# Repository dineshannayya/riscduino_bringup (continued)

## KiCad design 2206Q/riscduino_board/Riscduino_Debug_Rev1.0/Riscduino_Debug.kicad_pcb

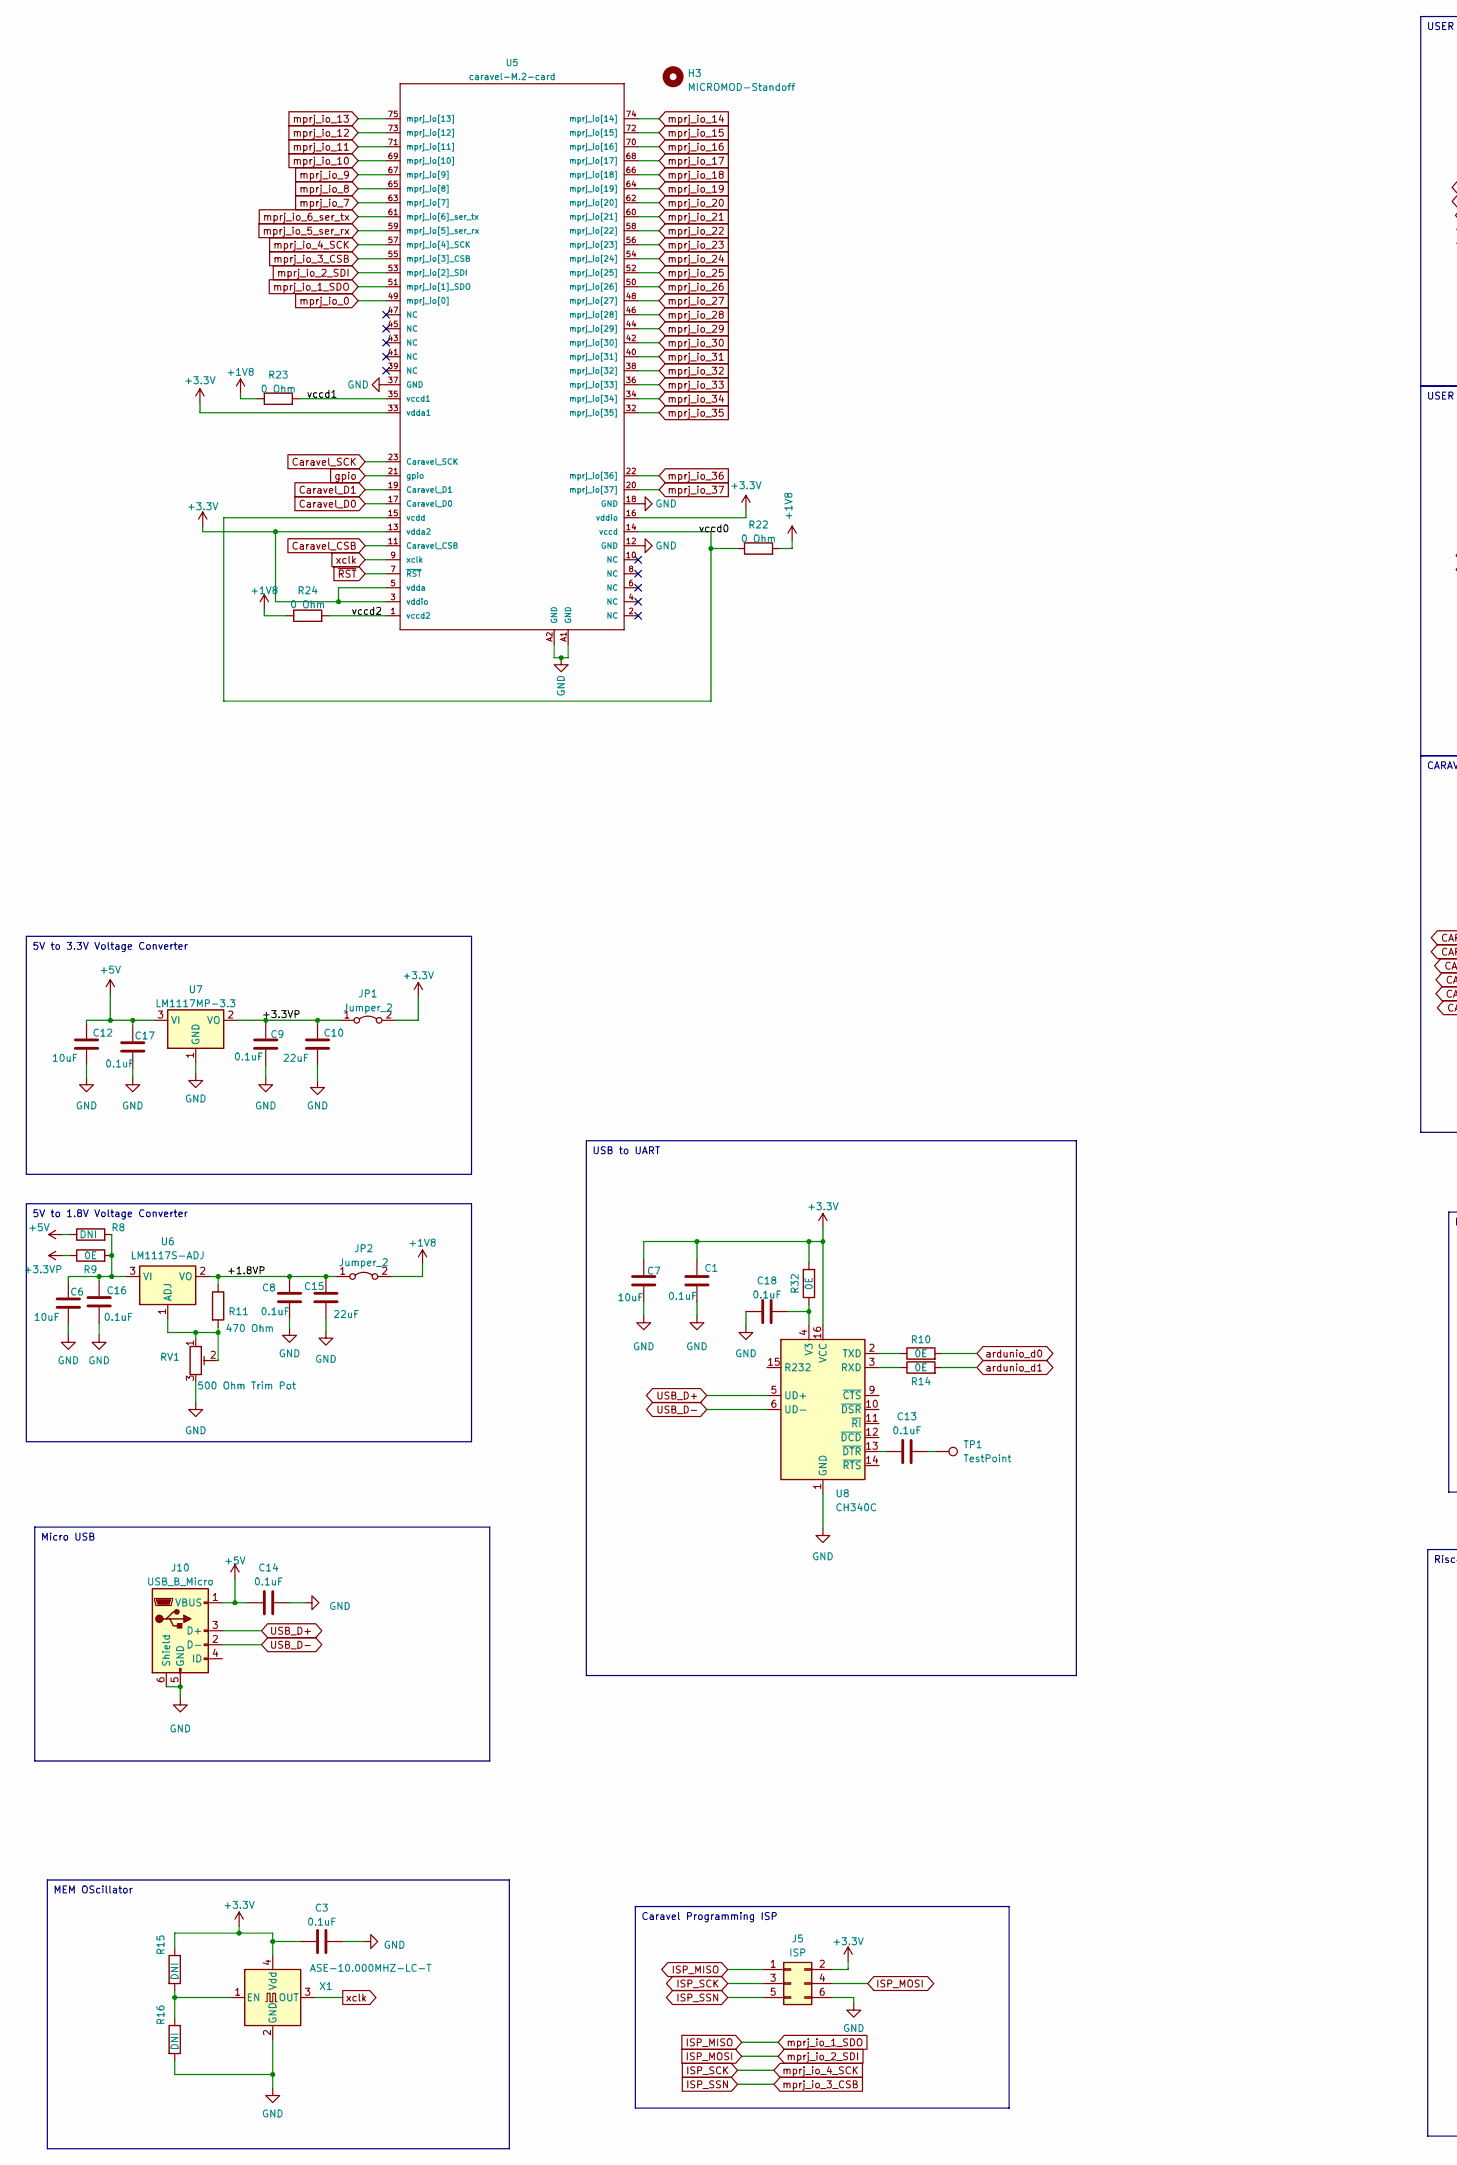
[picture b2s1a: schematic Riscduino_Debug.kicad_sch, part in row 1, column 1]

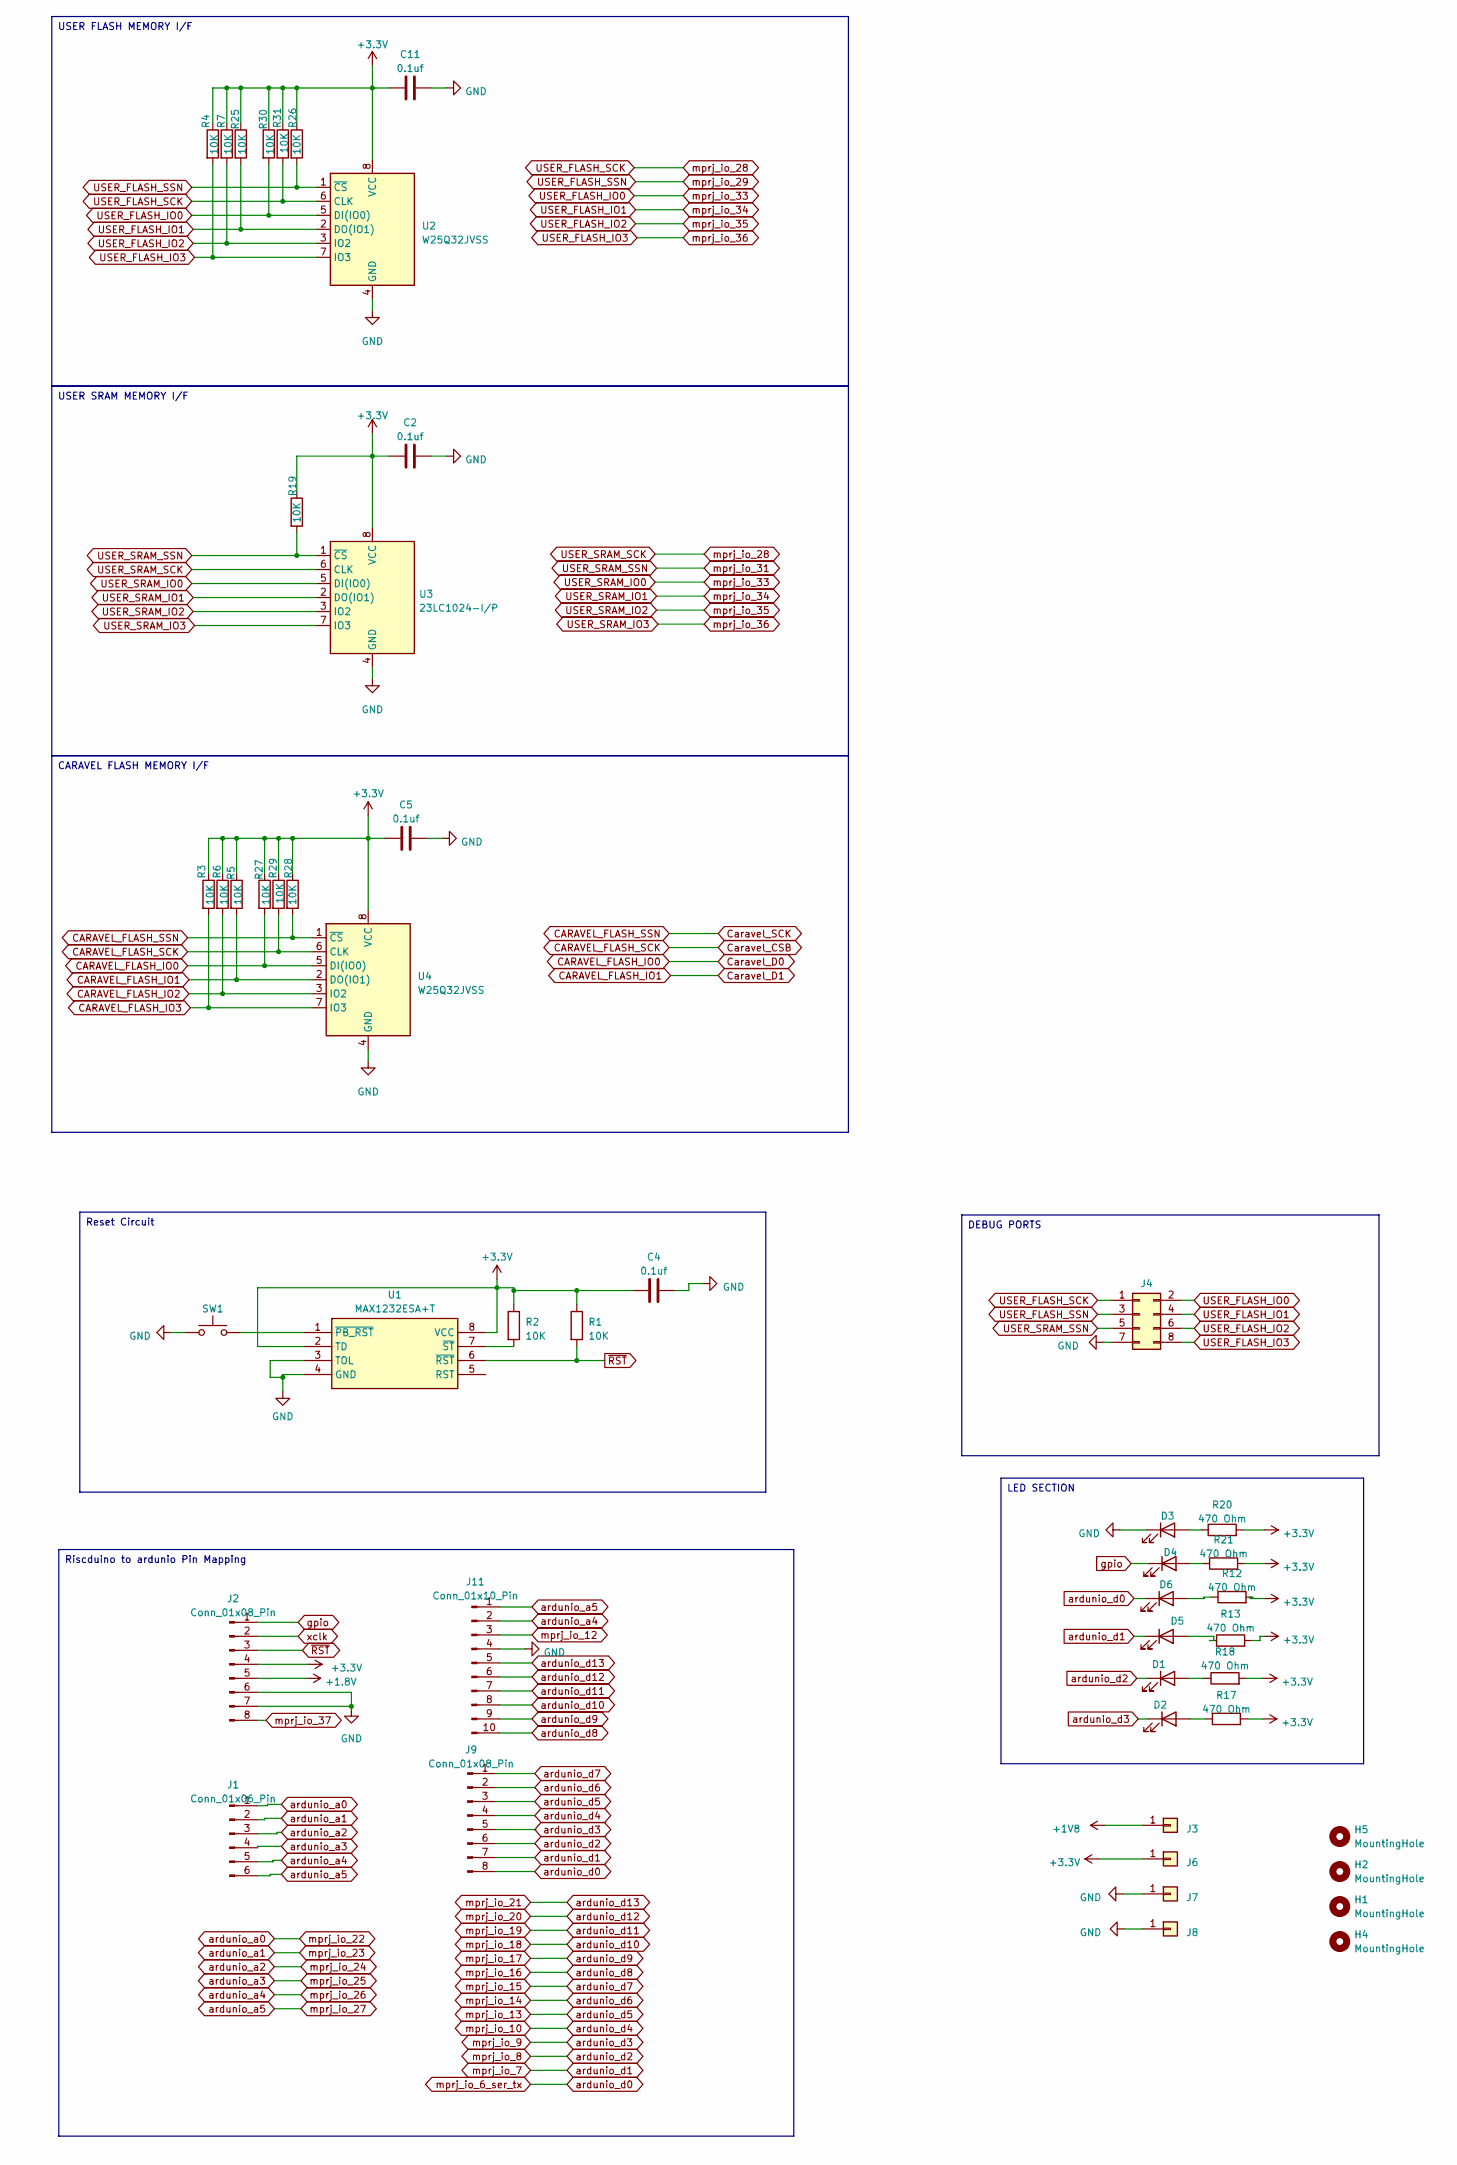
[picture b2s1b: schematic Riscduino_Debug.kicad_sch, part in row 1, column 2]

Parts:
C1, C3, C8, C9, C13, C14, C16, C17, C18: 0.1uF; C_0603_1608Metric_Pad1.08x0.95mm_HandSolder
C2, C4, C5, C11: 0.1uf; C_0603_1608Metric_Pad1.08x0.95mm_HandSolder
C6: 10uF; SW_SPST_CK_KXT3
C7, C12: 10uF; C_0805_2012Metric_Pad1.18x1.45mm_HandSolder
C10, C15: 22uF; C_0805_2012Metric_Pad1.18x1.45mm_HandSolder
D1, D2, D4, D5: GREEN LED; LED_0805_2012Metric_Pad1.15x1.40mm_HandSolder
D3: RED LED; LED_0805_2012Metric_Pad1.15x1.40mm_HandSolder
D6: BLUE LED; LED_0805_2012Metric_Pad1.15x1.40mm_HandSolder
H1, H2, H4, H5: MountingHole; MountingHole_3.2mm_M3
H3: MICROMOD-Standoff; MicroMod-Standoff
J1: Conn_01x06_Pin; PinHeader_1x06_P2.54mm_Vertical
J2, J9: Conn_01x08_Pin; PinHeader_1x08_P2.54mm_Vertical
J3, J6, J7, J8: Conn_01x01; PinHeader_1x01_P2.54mm_Vertical
J4: Conn_02x04_Odd_Even; PinHeader_2x04_P2.54mm_Vertical
J5: ISP; PinHeader_2x03_P2.54mm_Vertical
J10: USB_B_Micro; USB_Micro-B_Molex-105017-0001
J11: Conn_01x10_Pin; PinHeader_1x10_P2.54mm_Vertical
JP1, JP2: Jumper_2; PinHeader_1x02_P2.54mm_Vertical
R1, R2, R3, R4, R5, R6, R7, R19, R25, R26, R27, R28, R29, R30, R31: 10K; R_0603_1608Metric_Pad0.98x0.95mm_HandSolder
R8, R15, R16: DNI; R_0603_1608Metric_Pad0.98x0.95mm_HandSolder
R9, R10, R14, R32: 0E; R_0603_1608Metric_Pad0.98x0.95mm_HandSolder
R11, R12, R13, R17, R18, R20, R21: 470 Ohm; R_0603_1608Metric_Pad0.98x0.95mm_HandSolder
R22, R23, R24: 0 Ohm; R_0603_1608Metric_Pad0.98x0.95mm_HandSolder
RV1: 500 Ohm Trim Pot; Potentiometer_Bourns_3296W_Vertical
SW1: 4Pin Round Button SPST Straight Tactile Switch SM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; SW_SPST_EVPBF_TS4550TP
TP1: TestPoint; PinHeader_1x01_P2.54mm_Vertical
U1: MAX1232ESA+T; SOIC-8-1EP_3.9x4.9mm_P1.27mm_EP2.29x3mm; Manufacturer_Part_Number MAX1232ESA+T; Mouser Part Number 700-MAX1232ESAT
U2, U4: W25Q32JVSS; SOIC-8_5.23x5.23mm_P1.27mm
U3: 23LC1024-I/P; DIP-8_W7.62mm_LongPads
U5: caravel-M.2-card; M.2-CONNECTOR-E
U6: LM1117S-ADJ; SOT-223-3_TabPin2
U7: LM1117MP-3.3; SOT-223-3_TabPin2
U8: CH340C; SOIC-16_3.9x9.9mm_P1.27mm
X1: ASE-10.000MHZ-LC-T; Crystal_SMD_Abracon_ABM8G-4Pin_3.2x2.5mm

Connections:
+3.3V: C1.1, C2.1, C3.1, C4.1, C5.1, C7.1, C11.1, J2.4, J5.2, J6.1, JP1.2 (B), R1.1, R2.1, R3.1, R4.1, R5.1, R6.1, R7.1, R12.2, R13.2, R15.1, R17.2, R18.2, R19.1, R20.2, R21.2, R25.1, R26.1, R27.1, R28.1, R29.1, R30.1, R31.1, R32.2, U1.2 (TD), U1.8 (VCC), U2.8 (VCC), U3.8 (VCC), U4.8 (VCC), U5.3 (vddio), U5.5 (vdda), U5.13 (vdda2), U5.16 (vddio), U5.33 (vdda1), U8.16 (VCC), X1.4 (Vdd)
+3.3VP: C9.1, C10.1, JP1.1 (A), R9.1, U7.2 (VO)
+5V: C12.1, C14.1, C17.1, J10.1 (VBUS), R8.1, U7.3 (VI)
/+1.8VP: C8.1, C15.1, JP2.1 (A), R11.1, U6.2 (VO)
CARAVEL_FLASH_IO0: R27.2, U4.5 (DI(IO0)), U5.17 (Caravel_D0)
CARAVEL_FLASH_IO1: R5.2, U4.2 (DO(IO1)), U5.19 (Caravel_D1)
CARAVEL_FLASH_IO2: R6.2, U4.3 (IO2)
CARAVEL_FLASH_IO3: R3.2, U4.7 (IO3)
CARAVEL_FLASH_SCK: R29.2, U4.6 (CLK), U5.11 (Caravel_CSB)
CARAVEL_FLASH_SSN: R28.2, U4.1 (~CS), U5.23 (Caravel_SCK)
GND: C1.2, C2.2, C3.2, C4.2, C5.2, C6.2, C7.2, C8.2, C9.2, C10.2, C11.2, C12.2, C14.2, C15.2, C16.2, C17.2, C18.1, D3.1 (K), J2.6, J2.7, J4.7, J5.6, J7.1, J8.1, J10.5 (GND), J10.6 (Shield), J11.4, R16.2, RV1.3, SW1.1, U1.3 (TOL), U1.4 (GND), U2.4 (GND), U3.4 (GND), U4.4 (GND), U5.12 (GND), U5.18 (GND), U5.37 (GND), U5.A1 (GND), U5.A2 (GND), U7.1 (GND), U8.1 (GND), X1.2 (GND)
ISP_MISO: J5.1, U5.51 (mprj_io[1]_SDO)
ISP_MOSI: J5.4, U5.53 (mprj_io[2]_SDI)
ISP_SCK: J5.3, U5.57 (mprj_io[4]_SCK)
ISP_SSN: J5.5, U5.55 (mprj_io[3]_CSB)
unnamed: C13.2, TP1.1
unnamed: D1.2 (A), R18.1
unnamed 17: D2.2 (A), R17.1; also elsewhere on the board
unnamed: D3.2 (A), R20.1
unnamed: D4.2 (A), R21.1
unnamed: D5.2 (A), R13.1
unnamed: D6.2 (A), R12.1
unnamed: SW1.2, U1.1 (~PB_RST)
unnamed: R2.2, U1.7 (~ST)
unnamed: R23.2, U5.35 (vccd1)
unnamed: R24.2, U5.1 (vccd2)
unnamed: R22.1, U5.14 (vccd), U5.15 (vcdd)
unnamed: R11.2, RV1.1, RV1.2, U6.1 (ADJ)
unnamed: C6.1, C16.1, R8.2, R9.2, U6.3 (VI)
unnamed: R14.1, U8.3 (RXD)
unnamed: R10.1, U8.2 (TXD)
unnamed: C18.2, R32.1, U8.4 (V3)
unnamed: C13.1, U8.13 (~DTR)
unnamed: R15.2, R16.1, X1.1 (EN)
USB_D+: J10.3 (D+), U8.5 (UD+)
USB_D-: J10.2 (D-), U8.6 (UD-)
USER_FLASH_IO0: J4.2, R30.2, U2.5 (DI(IO0)), U3.5 (DI(IO0)), U5.36 (mprj_io[33])
USER_FLASH_IO1: J4.4, R25.2, U2.2 (DO(IO1)), U3.2 (DO(IO1)), U5.34 (mprj_io[34])
USER_FLASH_IO2: J4.6, R7.2, U2.3 (IO2), U3.3 (IO2), U5.32 (mprj_io[35])
USER_FLASH_IO3: J4.8, R4.2, U2.7 (IO3), U3.7 (IO3), U5.22 (mprj_io[36])
USER_FLASH_SCK: J4.1, R31.2, U2.6 (CLK), U3.6 (CLK), U5.46 (mprj_io[28])
USER_FLASH_SSN: J4.3, R26.2, U2.1 (~CS), U5.44 (mprj_io[29])
USER_SRAM_SSN: J4.5, R19.2, U3.1 (~CS), U5.40 (mprj_io[31])
ardunio_a0: J1.1, U5.58 (mprj_io[22])
ardunio_a1: J1.2, U5.56 (mprj_io[23])
ardunio_a2: J1.3, U5.54 (mprj_io[24])
ardunio_a3: J1.4, U5.52 (mprj_io[25])
ardunio_a4: J1.5, J11.2, U5.50 (mprj_io[26])
ardunio_a5: J1.6, J11.1, U5.48 (mprj_io[27])
ardunio_d0: D6.1 (K), J9.8, R10.2, U5.61 (mprj_io[6]_ser_tx)
ardunio_d1: D5.1 (K), J9.7, R14.2, U5.63 (mprj_io[7])
ardunio_d2: D1.1 (K), J9.6, U5.65 (mprj_io[8])
ardunio_d3: D2.1 (K), J9.5, U5.67 (mprj_io[9]), U8.67; also elsewhere on the board
ardunio_d4: J9.4, U5.69 (mprj_io[10])
ardunio_d5: J9.3, U5.75 (mprj_io[13])
ardunio_d6: J9.2, U5.74 (mprj_io[14])
ardunio_d7: J9.1, U5.72 (mprj_io[15])
ardunio_d8: J11.10, U5.70 (mprj_io[16])
ardunio_d9: J11.9, U5.68 (mprj_io[17])
ardunio_d10: J11.8, U5.66 (mprj_io[18])
ardunio_d11: J11.7, U5.64 (mprj_io[19])
ardunio_d12: J11.6, U5.62 (mprj_io[20])
ardunio_d13: J11.5, U5.60 (mprj_io[21])
gpio: D4.1 (K), J2.1, U5.21 (gpio)
mprj_io_0: U5.49 (mprj_io[0])
mprj_io_5_ser_rx: U5.59 (mprj_io[5]_ser_rx)
mprj_io_11: U5.71 (mprj_io[11])
mprj_io_12: J11.3, U5.73 (mprj_io[12])
mprj_io_30: U5.42 (mprj_io[30])
mprj_io_32: U5.38 (mprj_io[32])
mprj_io_37: J2.8, U5.20 (mprj_io[37])
xclk: J2.2, U5.9 (xclk), X1.3 (OUT)
~RST: J2.3, R1.2, U1.6 (~RST), U5.7 (~RST)

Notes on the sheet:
MEM OScillator
5V to 3.3V Voltage Converter
LED SECTION
Riscduino to ardunio Pin Mapping
Micro USB
USB to UART
USER SRAM MEMORY I/F
DEBUG PORTS
Caravel Programming ISP
USER FLASH MEMORY I/F
5V to 1.8V Voltage Converter
Reset Circuit
CARAVEL FLASH MEMORY I/F

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
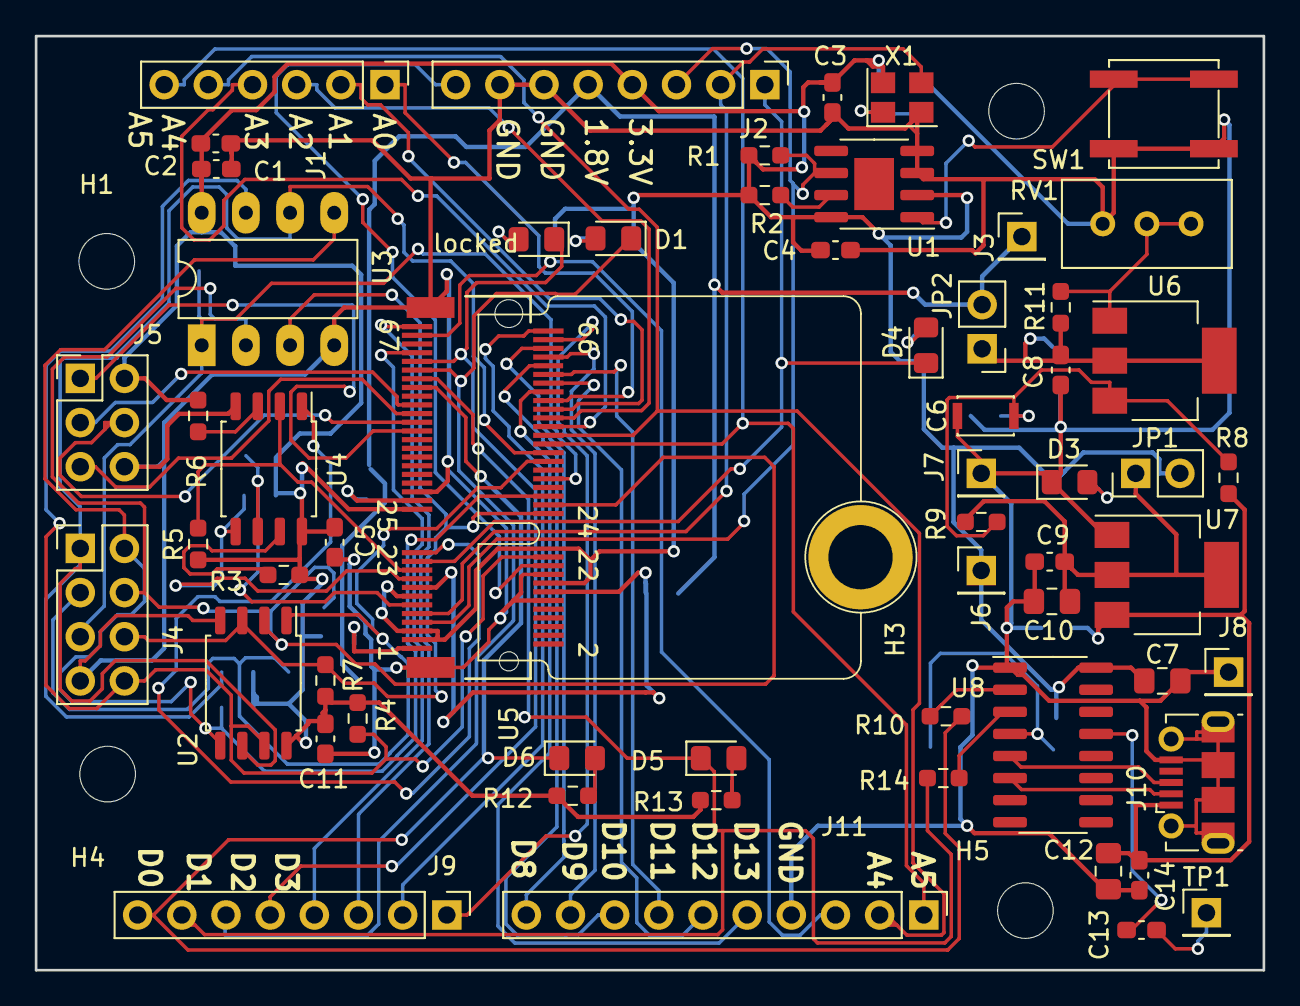
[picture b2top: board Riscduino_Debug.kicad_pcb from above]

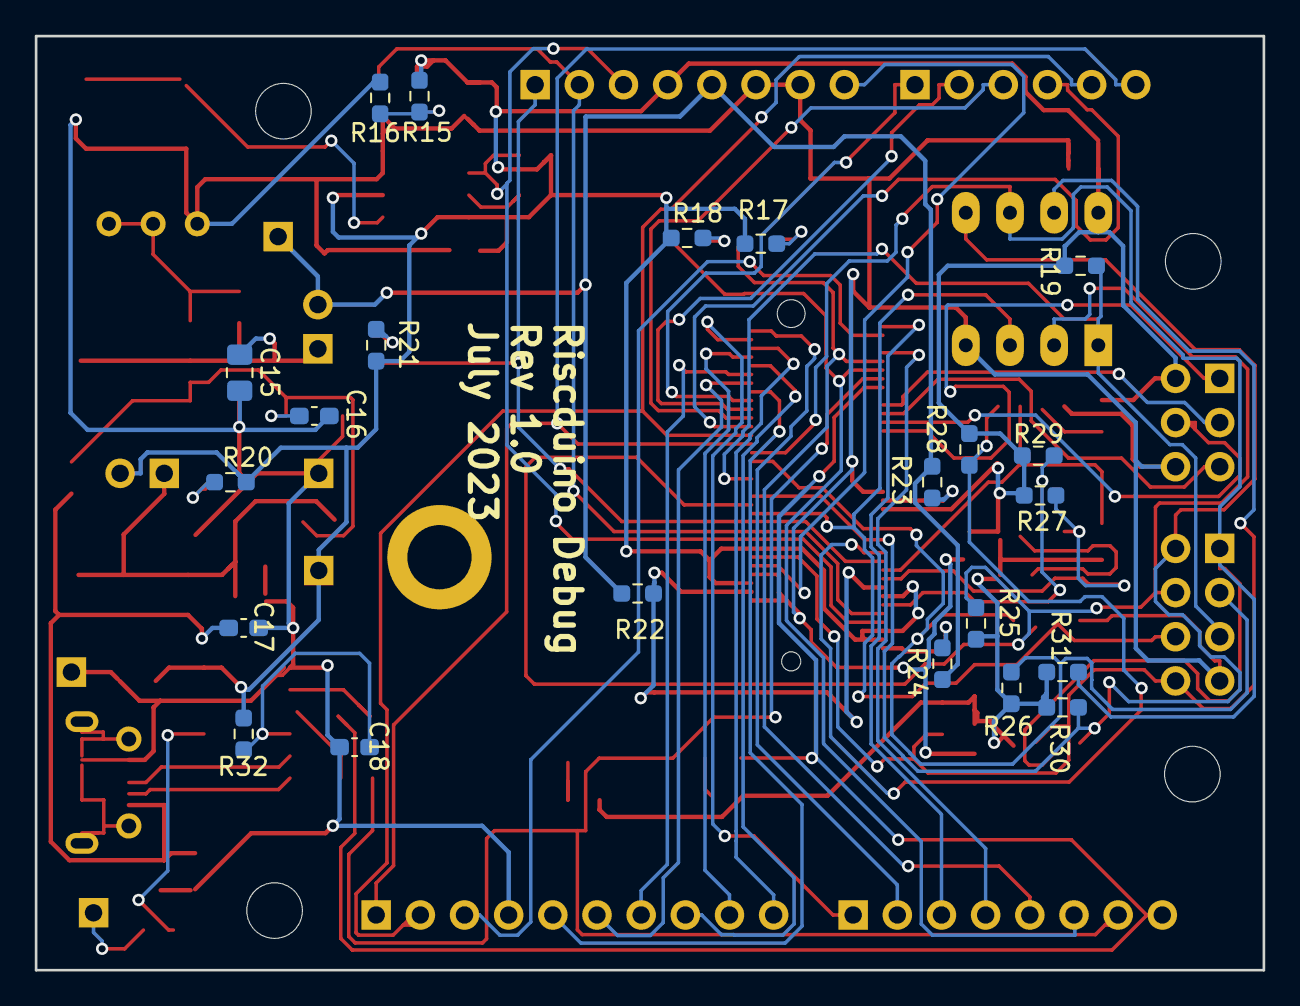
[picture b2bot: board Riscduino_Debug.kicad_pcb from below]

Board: 2 copper layers, 70.6 x 53.7 mm, 86 parts (22 on the bottom side), 69 nets.

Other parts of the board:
locked: GREEN LED; LED_0805_2012Metric_Pad1.15x1.40mm_HandSolder

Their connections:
unnamed 17: locked.2 (A); also elsewhere on the board
ardunio_d3: locked.1 (K); also elsewhere on the board

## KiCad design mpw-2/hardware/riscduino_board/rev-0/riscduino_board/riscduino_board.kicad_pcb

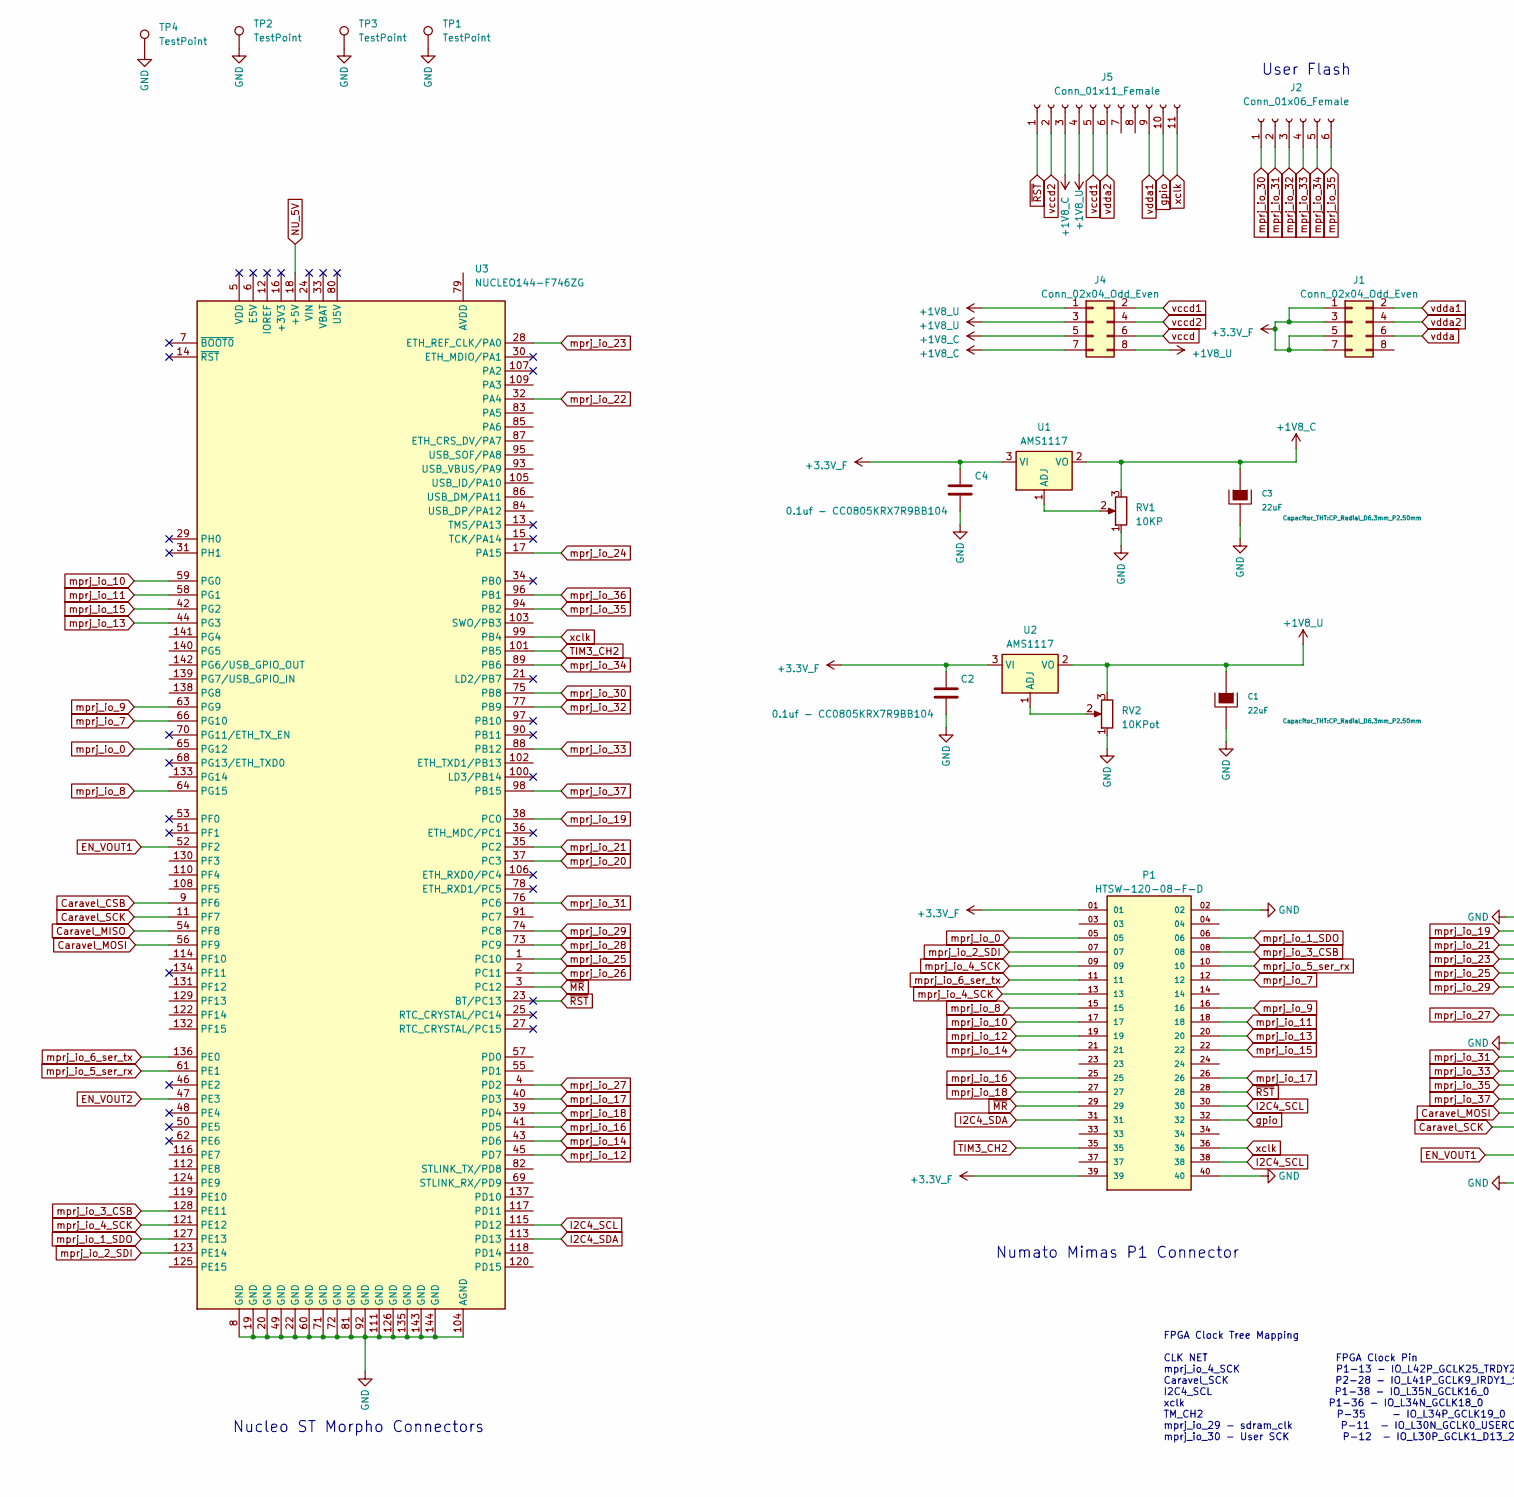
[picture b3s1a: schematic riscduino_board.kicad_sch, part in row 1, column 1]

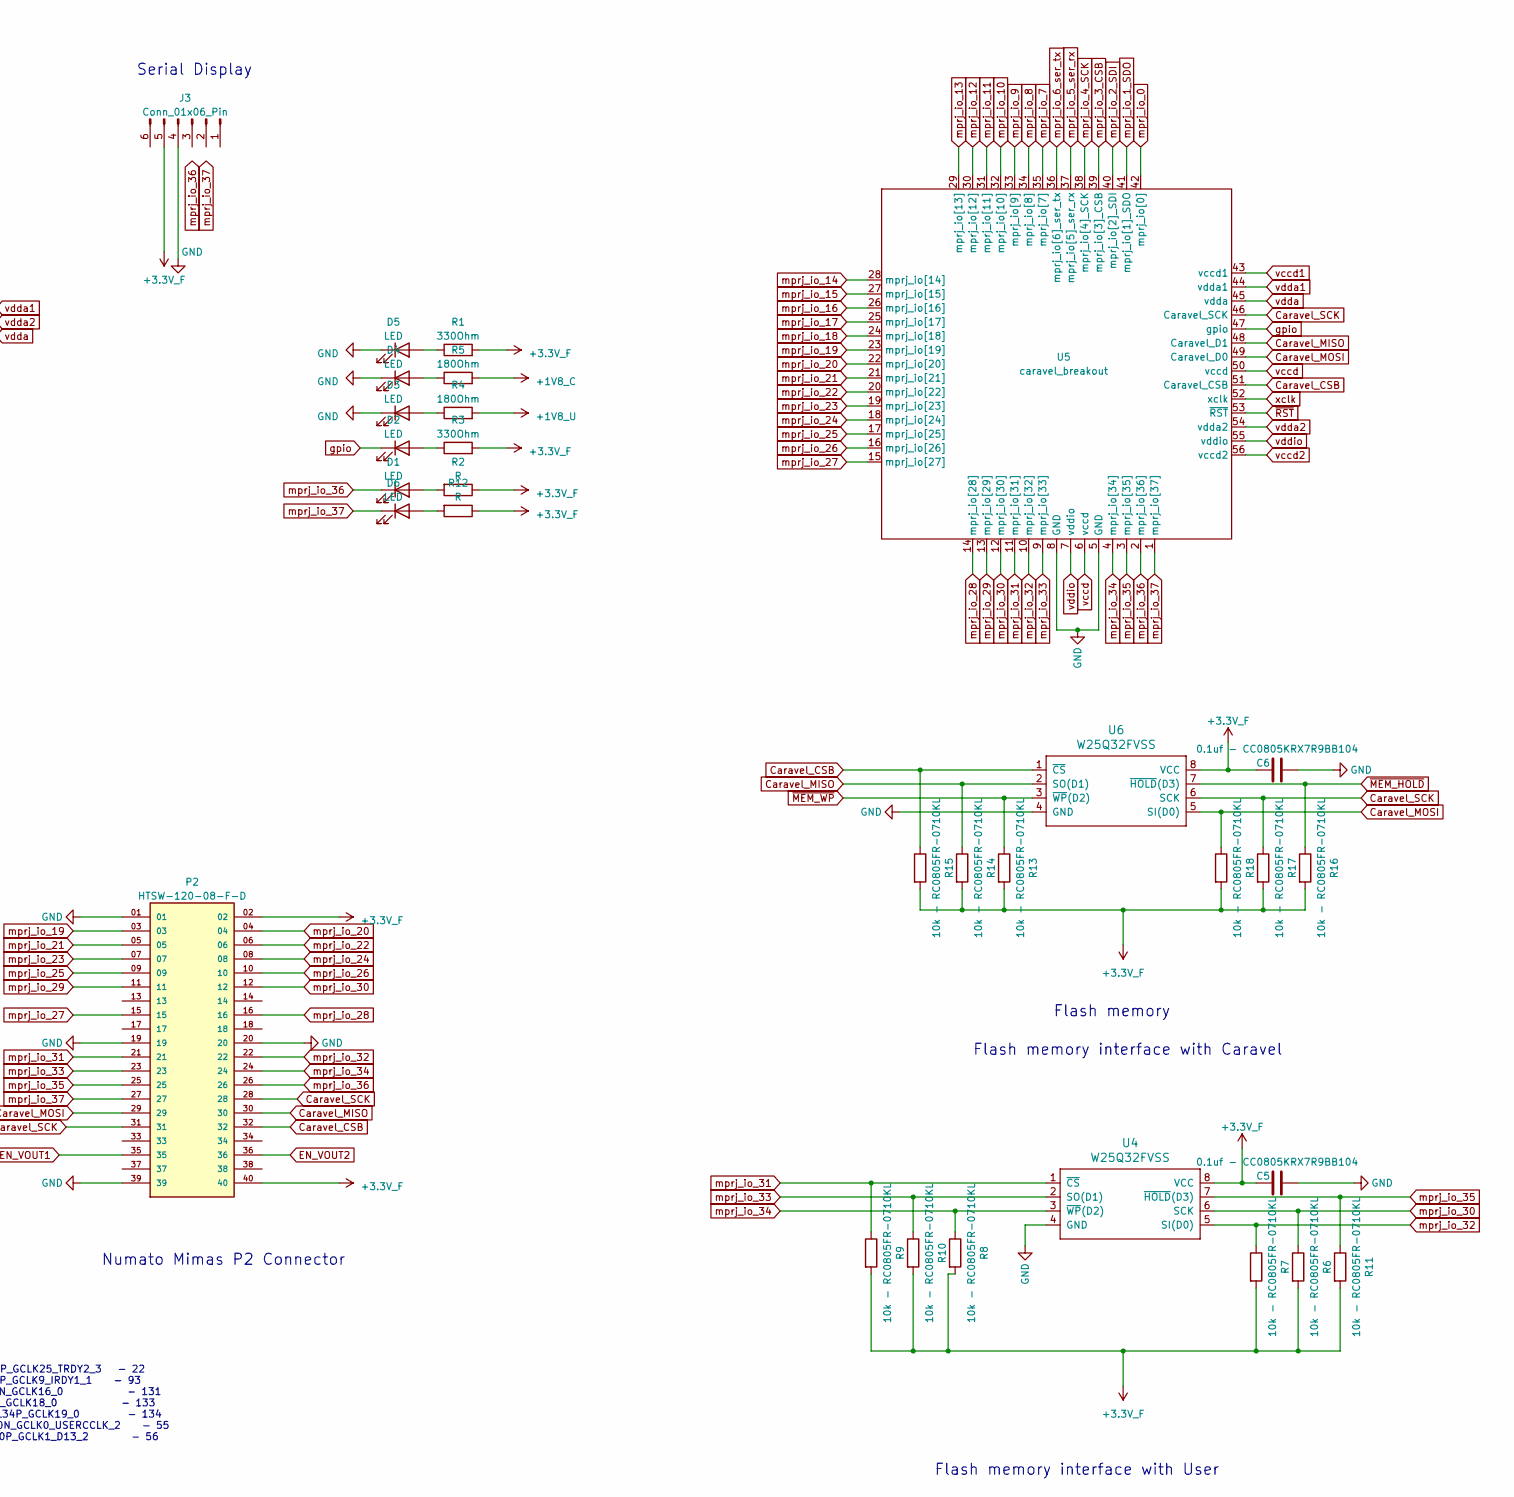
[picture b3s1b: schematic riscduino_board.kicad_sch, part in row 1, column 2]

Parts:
C1, C3: 22uF; CP_Radial_D6.3mm_P2.50mm
C2, C4, C5, C6: 0.1uf - CC0805KRX7R9BB104; C_1206_3216Metric
D1, D2, D3, D4, D5, D6: LED; LED_1206_3216Metric
J1, J4: Conn_02x04_Odd_Even; PinHeader_2x04_P2.54mm_Vertical
J2: Conn_01x06_Female; PinHeader_1x06_P2.54mm_Vertical
J3: Conn_01x06_Pin; PinHeader_1x06_P2.54mm_Vertical
J5: Conn_01x11_Female; PinHeader_1x11_P2.54mm_Vertical
P1, P2: HTSW-120-08-F-D; SAMTEC_HTSW-120-08-F-D; PARTREV R
R1, R3: 330Ohm; R_1206_3216Metric
R2, R12: R; R_1206_3216Metric
R4, R5: 180Ohm; R_1206_3216Metric
R6, R7, R8, R9, R10, R11, R13, R14, R15, R16, R17, R18: 10k - RC0805FR-0710KL; R_1206_3216Metric
RV1: 10KP; TRIM_T73YU103KT20
RV2: 10KPot; TRIM_T73YU103KT20
TP1, TP2, TP3, TP4: TestPoint; TestPoint_Bridge_Pitch2.54mm_Drill1.0mm
U1, U2: AMS1117; SOT-223-3_TabPin2
U3: NUCLEO144-F746ZG; ST_Morpho_Connectors_144
U4, U6: W25Q32FVSS; SOIC127P790X216-8N
U5: caravel_breakout; caravel_breakout_flexy_rev3D

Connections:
+1V8_C: C3.1, J4.5, J4.7, J5.3, R5.2, RV1.3, U1.2 (VO)
+1V8_U: C1.1, J4.1, J4.3, J4.8, J5.4, R4.2, RV2.3, U2.2 (VO)
+3.3V_F: C2.1, C4.1, C5.1, C6.1, J1.1, J1.3, J1.5, J1.7, J3.5, P1.01, P1.39, P2.02, P2.40, R1.2, R2.1, R3.2, R6.2, R7.2, R8.2, R9.2, R10.2, R11.2, R12.1, R13.2, R14.2, R15.2, R16.2, R17.2, R18.2, U1.3 (VI), U2.3 (VI), U4.8 (VCC), U6.8 (VCC)
Caravel_CSB: P2.32, R15.1, U3.9 (PF6), U5.51 (Caravel_CSB), U6.1 (~CS)
Caravel_MISO: P2.30, R14.1, U3.54 (PF8), U5.48 (Caravel_D1), U6.2 (SO(D1))
Caravel_MOSI: P2.29, R18.1, U3.56 (PF9), U5.49 (Caravel_D0), U6.5 (SI(D0))
Caravel_SCK: P2.28, P2.31, R17.1, U3.11 (PF7), U5.46 (Caravel_SCK), U6.6 (SCK)
EN_VOUT1: P2.35, U3.52 (PF2)
EN_VOUT2: P2.36, U3.47 (PE3)
GND: C1.2, C2.2, C3.2, C4.2, C5.2, C6.2, D3.1 (K), D4.1 (K), D5.1 (K), J3.4, P1.02, P1.40, P2.01, P2.19, P2.20, P2.39, RV1.1, RV2.1, TP1.1, TP2.1, TP3.1, TP4.1, U3.8 (GND), U3.19 (GND), U3.20 (GND), U3.22 (GND), U3.49 (GND), U3.60 (GND), U3.71 (GND), U3.72 (GND), U3.81 (GND), U3.92 (GND), U3.104 (AGND), U3.111 (GND), U3.126 (GND), U3.135 (GND), U3.143 (GND), U3.144 (GND), U4.4 (GND), U5.5 (GND), U5.8 (GND), U6.4 (GND)
I2C4_SCL: P1.30, P1.38, U3.115 (PD12)
I2C4_SDA: P1.31, U3.113 (PD13)
NU_5V: U3.18 (+5V)
unnamed: D1.2 (A), R2.2
unnamed: D2.2 (A), R3.1
unnamed: D3.2 (A), R4.1
unnamed: D4.2 (A), R5.1
unnamed: D5.2 (A), R1.1
unnamed: D6.2 (A), R12.2
unnamed: RV1.2, U1.1 (ADJ)
unnamed: RV2.2, U2.1 (ADJ)
TIM3_CH2: P1.35, U3.101 (PB5)
gpio: D2.1 (K), J5.10, P1.32, U5.47 (gpio)
mprj_io_0: P1.05, U3.65 (PG12), U5.42 (mprj_io[0])
mprj_io_1_SDO: P1.06, U3.127 (PE13), U5.41 (mprj_io[1]_SDO)
mprj_io_2_SDI: P1.07, U3.123 (PE14), U5.40 (mprj_io[2]_SDI)
mprj_io_3_CSB: P1.08, U3.128 (PE11), U5.39 (mprj_io[3]_CSB)
mprj_io_4_SCK: P1.09, P1.13, U3.121 (PE12), U5.38 (mprj_io[4]_SCK)
mprj_io_5_ser_rx: P1.10, U3.61 (PE1), U5.37 (mprj_io[5]_ser_rx)
mprj_io_6_ser_tx: P1.11, U3.136 (PE0), U5.36 (mprj_io[6]_ser_tx)
mprj_io_7: P1.12, U3.66 (PG10), U5.35 (mprj_io[7])
mprj_io_8: P1.15, U3.64 (PG15), U5.34 (mprj_io[8])
mprj_io_9: P1.16, U3.63 (PG9), U5.33 (mprj_io[9])
mprj_io_10: P1.17, U3.59 (PG0), U5.32 (mprj_io[10])
mprj_io_11: P1.18, U3.58 (PG1), U5.31 (mprj_io[11])
mprj_io_12: P1.19, U3.45 (PD7), U5.30 (mprj_io[12])
mprj_io_13: P1.20, U3.44 (PG3), U5.29 (mprj_io[13])
mprj_io_14: P1.21, U3.43 (PD6), U5.28 (mprj_io[14])
mprj_io_15: P1.22, U3.42 (PG2), U5.27 (mprj_io[15])
mprj_io_16: P1.25, U3.41 (PD5), U5.26 (mprj_io[16])
mprj_io_17: P1.26, U3.40 (PD3), U5.25 (mprj_io[17])
mprj_io_18: P1.27, U3.39 (PD4), U5.24 (mprj_io[18])
mprj_io_19: P2.03, U3.38 (PC0), U5.23 (mprj_io[19])
mprj_io_20: P2.04, U3.37 (PC3), U5.22 (mprj_io[20])
mprj_io_21: P2.05, U3.35 (PC2), U5.21 (mprj_io[21])
mprj_io_22: P2.06, U3.32 (PA4), U5.20 (mprj_io[22])
mprj_io_23: P2.07, U3.28 (ETH_REF_CLK/PA0), U5.19 (mprj_io[23])
mprj_io_24: P2.08, U3.17 (PA15), U5.18 (mprj_io[24])
mprj_io_25: P2.09, U3.1 (PC10), U5.17 (mprj_io[25])
mprj_io_26: P2.10, U3.2 (PC11), U5.16 (mprj_io[26])
mprj_io_27: P2.15, U3.4 (PD2), U5.15 (mprj_io[27])
mprj_io_28: P2.16, U3.73 (PC9), U5.14 (mprj_io[28])
mprj_io_29: P2.11, U3.74 (PC8), U5.13 (mprj_io[29])
mprj_io_30: J2.1, P2.12, R6.1, U3.75 (PB8), U4.6 (SCK), U5.12 (mprj_io[30])
mprj_io_31: J2.2, P2.21, R9.1, U3.76 (PC6), U4.1 (~CS), U5.11 (mprj_io[31])
mprj_io_32: J2.3, P2.22, R7.1, U3.77 (PB9), U4.5 (SI(D0)), U5.10 (mprj_io[32])
mprj_io_33: J2.4, P2.23, R10.1, U3.88 (PB12), U4.2 (SO(D1)), U5.9 (mprj_io[33])
mprj_io_34: J2.5, P2.24, R8.1, U3.89 (PB6), U4.3 (~WP(D2)), U5.4 (mprj_io[34])
mprj_io_35: J2.6, P2.25, R11.1, U3.94 (PB2), U4.7 (~HOLD(D3)), U5.3 (mprj_io[35])
mprj_io_36: D1.1 (K), P2.26, U3.96 (PB1), U5.2 (mprj_io[36])
mprj_io_37: D6.1 (K), P2.27, U3.98 (PB15), U5.1 (mprj_io[37])
vccd: J4.6, U5.6 (vccd), U5.50 (vccd)
vccd1: J4.2, J5.5, U5.43 (vccd1)
vccd2: J4.4, J5.2, U5.56 (vccd2)
vdda: J1.6, U5.45 (vdda)
vdda1: J1.2, J5.9, U5.44 (vdda1)
vdda2: J1.4, J5.6, U5.54 (vdda2)
vddio: U5.7 (vddio), U5.55 (vddio)
xclk: J5.11, P1.36, U3.99 (PB4), U5.52 (xclk)
~MEM_HOLD: R16.1, U6.7 (~HOLD(D3))
~MEM_WP: R13.1, U6.3 (~WP(D2))
~MR: P1.29, U3.3 (PC12)
~RST: J5.1, P1.28, U3.23 (BT/PC13), U5.53 (~RST)

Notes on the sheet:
Numato Mimas P1 Connector
Flash memory
Serial Display
Numato Mimas P2 Connector
User Flash
Nucleo ST Morpho Connectors
FPGA Clock Tree Mapping CLK NET FPGA Clock Pin mprj_io_4_SCK P1-13 - IO_L42P_GCLK25_TRDY2_3 - 22 Caravel_SCK P2-28 - IO_L41P_GCLK9_IRDY1_1 - 93 I2C4_SCL P1-38 - IO_L35N_GCLK16_0 - 131 xclk P1-36 - IO_L34N_GCLK18_0 - 133 TM_CH2 P-35 - IO_L34P_GCLK19_0 - 134 mprj_io_29 - sdram_clk P-11 - IO_L30N_GCLK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
Flash memory interface with User
Flash memory interface with Caravel

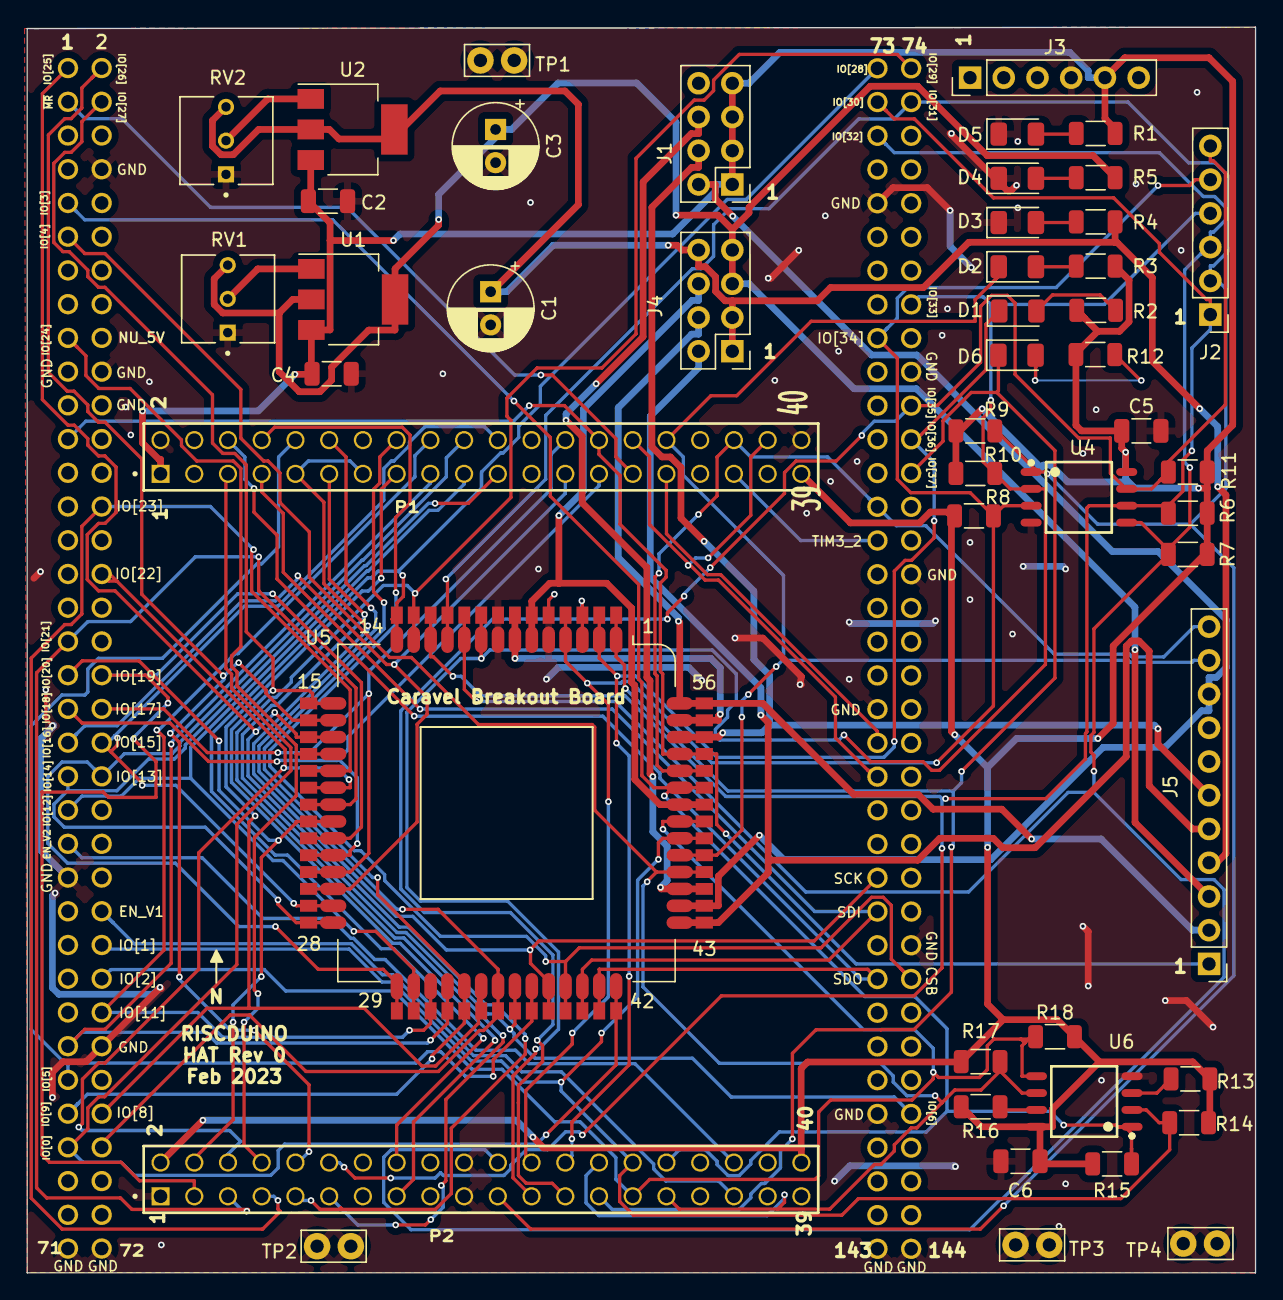
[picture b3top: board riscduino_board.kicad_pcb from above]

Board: 2 copper layers, 92.5 x 93.8 mm, 49 parts (0 on the bottom side), 72 nets.
